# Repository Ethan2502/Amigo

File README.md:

# Amigo

A desk companion cube that takes over the things you unlock your phone for, so you have no reason to pick it up.

## Why I made it

This is my project that I got an idea for when my phone's alarm went off. I always tend to use my phone a little bit in bed when I wake up. I thought I needed my phone to wake me up but then I thought of a product that replaced all the "utility" items your phone could do but without the distractions. I used screentime apps before but they always make it in fingers reach to disable it. Amigo takes the other approach. Instead of locking the phone down, it takes over the jobs you unlock the phone for in the first place, so there is nothing to reach for.

Physically locking the phone away is something I want to add later. The current design does not do it.

## What it does

1. **Wakes you up.** Alarm clock, so your phone doesn't have to be the thing next to your bed.
2. **Keeps your phone down.** The alarm, timer, and display all live on the cube, so there is no reason to unlock your phone for any of them.
3. **Utility stuff.** Timers, stopwatch, and the other simple things you'd normally pull your phone out for.
4. **Desk toy.** Displays pictures on a slide deck while you work.
5. **Classroom toy.** Small kids in elementary school can use it to develop cognitive function with memory games or reaction time tests. It can teach them things through games where they answer questions using the keypad as arrows or other controls to move, fight, and so on. It's a lot cheaper than buying a brand new computer or phone, so it's a budget friendly classroom toy.

## How it works

Amigo is two PCBs and a 3D printed case.

The **main board** carries an ESP32-S3-WROOM-1, a TP4056 LiPo charger, an AP2112K 3.3 V LDO, and headers for the display, the audio amp, the power switch, and the button matrix. It runs off a single-cell LiPo and charges over USB-C.

The **3x3 button matrix board** is a separate PCB with nine Kailh Choc hotswap switches and nine 1N4148W diodes in a standard row/column matrix, so nine keys read over six GPIO. It connects to the main board through an 8-pin ribbon header.

## Repo layout

```
hardware/
  main-board/          KiCad project for the ESP32-S3 main board
    production/        gerbers, BOM, pick-and-place files
  button-matrix/       KiCad project for the 3x3 switch board
    libs/              Keebio-Parts footprint library (third party, see credits)
    production/
cad/
  amigo.f3z            Fusion 360 Archive file for multi-component assemblies
  step/                STEP exports
  stl/                 printable parts
docs/                  assembly instructions
firmware/              (in progress)
images/                renders and photos
bom.csv                full bill of materials
```

## Assembly

### 1. Order the PCBs

Send `hardware/main-board/production/gerbers.zip` and `hardware/button-matrix/production/gerbers.zip` to your fab house. Both are 2-layer, 1.6 mm.

You can use PCBA to save time on soldering. If you don't it will be harder and you may or may not have to make a stencil. I ordered PCBA

### 2. Print the case

| Part | File | Notes |
| --- | --- | --- |
| Case | `cad/stl/case.stl` | Needs supports |
| Button cover | `cad/stl/button-cover.stl` | 10% Gyroid |
| Display mount | `cad/stl/display-mount.stl` | 10% Gyroid |
| Keycaps | `cad/stl/keycaps.stl` | x9 10% Gyroid |

Settings I used:
1. Gyroid Infill at 10%
2. Supports only on the case
3. The rest I used bambu slicer and their default settings for PLA

### 3. Solder the main board

If you ordered PCBA then skip. 

Use solder paste, wick, and flux to do solder. I believe using a stencil will make applying solder paste easier but I ordered PCBA. Solder all the parts on to it and also
don’t forget things like key caps for the buttons. Refer to Ki Cad files as
instructions for each cap or resistor and anything else you may need. 

Also the ESP board and the TP4056 should probably be soldered first because they are the most finicky. The TP4056 also has a thermal pad underneath. I suggest soldering all the passives like capacitators and resistors last.

### 4. Solder the button matrix

When you solder the button matrix it is important to make sure your diodes are the right direction. Normally when assmbling things I find it easier to have the file open whether it be a CAD or a PCB design. This way it is concrete in exactly what direction you planned for it earlier. Also don't forget keycaps while soldering.

### 5. Wire the modules

Again you can pull up the file to see which way the order is for the pin connectors. You can then work through it wire by wire by counting. This is the most concrete way to do it withought messing up. To be extra secure you can use some hot glue and secure the connection. 

### 6. Assemble the Cube

Use M3 screws and nuts to screw everything in. There should be a hole for each screw.

### 7. Flash the Firmware

Once firmware is written you can flash it. I have not written it yet I will update it later.

## Bill of Materials

Prices are per-unit at the quantity needed to build one Amigo. Several LCSC parts have minimum order quantities well above what the board uses (the 0603 passives ship in reels of 50 or 100), so the actual amount you spend at checkout will be higher than the totals below.

The main board was ordered as PCBA, so the surface-mount parts in the first table were supplied to the assembler rather than hand-soldered. The button matrix board was ordered bare and assembled by hand.

### Main board

| Ref | Part | Qty | Unit | Total | Link |
| --- | --- | --- | --- | --- | --- |
| U3 | ESP32-S3-WROOM-1-N16R8 | 1 | $5.16 | $5.16 | [C2913202](https://www.lcsc.com/product-detail/C2913202.html) |
| U1 | TP4056-42-ESOP8 LiPo charger (ESOP-8) | 1 | $0.19 | $0.19 | [C16581](https://www.lcsc.com/product-detail/C16581.html) |
| U2 | AP2112K-3.3TRG1 LDO (SOT-23-5) | 1 | $0.11 | $0.11 | [C23380830](https://www.lcsc.com/product-detail/C23380830.html) |
| J1 | USB4085-GF-A USB-C receptacle | 1 | $1.42 | $1.42 | [C7095263](https://www.lcsc.com/product-detail/C7095263.html) |
| J2 | S2B-PH-K-S-GW JST PH 2-pin, right angle | 1 | $0.18 | $0.18 | [C157932](https://www.lcsc.com/product-detail/C157932.html) |
| J3 | PPTC081LFBN-RC female header 1x08 2.54 mm (display) | 1 | $1.54 | $1.54 | [C3320851](https://www.lcsc.com/product-detail/C3320851.html) |
| J4 | PPTC071LFBN-RC female header 1x07 2.54 mm (audio amp) | 1 | $0.79 | $0.79 | [C5342086](https://www.lcsc.com/product-detail/C5342086.html) |
| J5 | PRPC002SAAN-RC pin header 1x02 2.54 mm (power switch) | 1 | $0.09 | $0.09 | [C3346540](https://www.lcsc.com/product-detail/C3346540.html) |
| J6 | PPTC081LFBN-RC female header 1x08 2.54 mm (button ribbon) | 1 | $1.54 | $1.54 | [C3320851](https://www.lcsc.com/product-detail/C3320851.html) |
| SW1, SW2 | TL3342F260QG tactile switch | 2 | $1.15 | $2.29 | [C2886894](https://www.lcsc.com/product-detail/C2886894.html) |
| D1 | YLED0805G green LED, 0805 | 1 | $0.01 | $0.01 | [C25170728](https://www.lcsc.com/product-detail/C25170728.html) |
| D2 | YLED0805B blue LED, 0805 | 1 | $0.01 | $0.01 | [C19273154](https://www.lcsc.com/product-detail/C19273154.html) |
| D3 | YLED0805R red LED, 0805 | 1 | $0.01 | $0.01 | [C19171391](https://www.lcsc.com/product-detail/C19171391.html) |
| C1, C2, C3, C11 | 10 µF 25 V X5R, 0603 | 4 | $0.48 | $1.92 | [C344022](https://www.lcsc.com/product-detail/C344022.html) |
| C4, C6, C9, C10 | 100 nF 50 V X7R, 0603 | 4 | $0.02 | $0.08 | [C14663](https://www.lcsc.com/product-detail/C14663.html) |
| C5, C7, C8 | 1 µF 25 V X7R, 0603 | 3 | $0.02 | $0.07 | [C29936](https://www.lcsc.com/product-detail/C29936.html) |
| R1, R2 | 5.1 kΩ 1%, 0603 | 2 | $0.01 | $0.01 | [C105580](https://www.lcsc.com/product-detail/C105580.html) |
| R3 | 2 kΩ 5%, 0603 | 1 | $0.01 | $0.01 | [C105581](https://www.lcsc.com/product-detail/C105581.html) |
| R4, R5 | 100 kΩ 1%, 0603 | 2 | $0.01 | $0.01 | [C14675](https://www.lcsc.com/product-detail/C14675.html) |
| R6, R7 | 10 kΩ 1%, 0603 | 2 | $0.01 | $0.01 | [C98220](https://www.lcsc.com/product-detail/C98220.html) |
| R10, R11, R12 | 1 kΩ 1%, 0603 | 3 | $0.01 | $0.02 | [C22548](https://www.lcsc.com/product-detail/C22548.html) |
| | **Main board subtotal** | | | **$15.47** | |

### Button matrix board

| Ref | Part | Qty | Unit | Total | Link |
| --- | --- | --- | --- | --- | --- |
| CHOC1-CHOC9 | Kailh Choc low profile hotswap socket | 9 | $0.78 | $7.02 | [Amazon](https://www.amazon.com/Mechkeeb-Kailh-Low-Hot-swappable-Socket/dp/B0BS3L174L) |
| | Kailh Choc low profile keyswitch | 9 | $1.92 | $17.28 | [Amazon](https://www.amazon.com/KAILH-Official-Chocolate-Mechanical-Keyboard/dp/B0B3MNBPSP) |
| D1-D9 | 1N4148W diode, SOD-123 | 9 | $0.01 | $0.08 | [C908248](https://www.lcsc.com/product-detail/C908248.html) |
| J1 | Header 1x08 2.54 mm (ribbon to main board) | 1 | $1.54 | $1.54 | [C3320851](https://www.lcsc.com/product-detail/C3320851.html) |
| R1, R2, R3 | 10 kΩ 1%, 0603 | 3 | $0.01 | $0.02 | [C98220](https://www.lcsc.com/product-detail/C98220.html) |
| | **Button matrix subtotal** | | | **$25.94** | |

Keycaps are 3D printed from `cad/stl/keycaps.stl`, so there is nothing to buy for them.

### Off-board parts

| Part | Qty | Unit | Total | Link |
| --- | --- | --- | --- | --- |
| HiLetgo 2.8 in ILI9341 SPI display, 240x320 | 1 | $16.39 | $16.39 | [Amazon](https://www.amazon.com/HiLetgo-240X320-Resolution-Display-ILI9341/dp/B073R7BH1B) |
| MAX98357A I2S audio amp breakout | 1 | $6.88 | $6.88 | [Amazon](https://www.amazon.com/MAX98357-MAX98357A-Amplifier-Interface-Raspberry/dp/B0DPJRLMDJ) |
| CQRobot speaker, JST-PH 2.0 mm interface | 1 | $7.99 | $7.99 | [Amazon](https://www.amazon.com/CQRobot-JST-PH2-0-Interface-Electronic-Projects/dp/B0738NLFTG) |
| EEMB 1100 mAh single-cell LiPo, JST connector | 1 | $6.15 | $6.15 | [Amazon](https://www.amazon.com/EEMB-1100mAh-Battery-Rechargeable-Connector/dp/B08VRYS8FT) |
| Rocker power switch | 1 | $1.35 | $1.35 | [AliExpress](https://www.aliexpress.us/item/3256812208202705.html) |
| Jumper wires, board-to-board ribbon link | 1 | $6.98 | $6.98 | [Amazon](https://www.amazon.com/Elegoo-EL-CP-004-Multicolored-Breadboard-arduino/dp/B01EV70C78) |
| PLA filament for case, button cover, display mount, keycaps | 1 | $20.00 | $20.00 | [Polymaker](https://shop.polymaker.com/products/polymaker-pla-pro?variant=41550910652473) |
| M3 screws and nuts pack of 100 | 1 | $15.30 | $15.30 | [McMaster](https://www.mcmaster.com/products/screws/socket-head-screws-2~/steel-socket-head-screws~~/?s=m3+screws) |
| PCB fabrication: main board PCBA and button matrix bare PCB | 1 | $50.65 | $50.65 | [JLCPCB](https://jlcpcb.com/) |
| | | | **$131.69 plus fasteners** | |

The Amazon parts ship in fixed pack sizes rather than the exact count the build uses. The Unit column is the per-item price and the Total is what one Amigo consumes, so your checkout total will be higher.

### Total

**$173.10 plus fasteners** to build one Amigo: $15.47 for the main board, $25.94 for the button matrix, and $116.39 in off-board parts and fabrication. Fabrication is the single largest line at $50.65.

## Tools used

Not part of the build, listed for anyone reproducing it.

| Tool | Link |
| --- | --- |
| Soldering iron | [Amazon](https://www.amazon.com/Wonderway-Soldering-Electronics-CELLPHONE-Repairing/dp/B0BLSJQPR6) |
| Desoldering pump | [Amazon](https://www.amazon.com/Lesnow-Desoldering-Electronics-Disassemble-Electrical/dp/B0F8BJPC9Y) |
| Multimeter | [Amazon](https://www.amazon.com/ANENG-Multimeter-Resistance-Continuity-Automotive/dp/B0BYD32JZV) |

## Firmware

Not written yet. The plan is firmware that lets people program the device, download or make games, and customize it for their needs, with over-the-wifi updates so the software keeps getting better.

## Credits

The `hardware/button-matrix/libs/Keebio-Parts.pretty-master` footprint library is Keebio's, used under its own license for the Kailh Choc footprints. Everything else in this repo is my own work.

## What I learned

I used a bunch of stuff on this project for the first time, like KiCad to make my PCBs. I realize how hard it is to actually verify if some PCB works before you order it. I guess it is because I didn't have a breadboard kit. Some of the most memorable things I learned about electronic design is things like not forgetting a fuse or remembering to add EN and Boot switches. I also learned to try and plan the actual product out before because I wanted motors to drive it but I didn't account for any sizing constraints and it turned out to be to out of reach for a first project.

I really enjoyed putting everything together at the end in Fusion with the actual CAD of the PCB. My least faveorite part was actually ordering everything because who knew things cost money! I didn't notice but my amazon cart added up quick and I made a switch to ali express and was able to save some money. JLC was also really annoying one day where it kept rejecting my files and it didn't work and I had to restart the entire process from scratch to try and debug it. Another thing I learned while ordering was the company LCSC sells parts but it takes time to quote it. They sent me an email but I didn't check it so I forgot to actually order it! Overall I am excited to assmble this thing I have been working on for a long time.

---

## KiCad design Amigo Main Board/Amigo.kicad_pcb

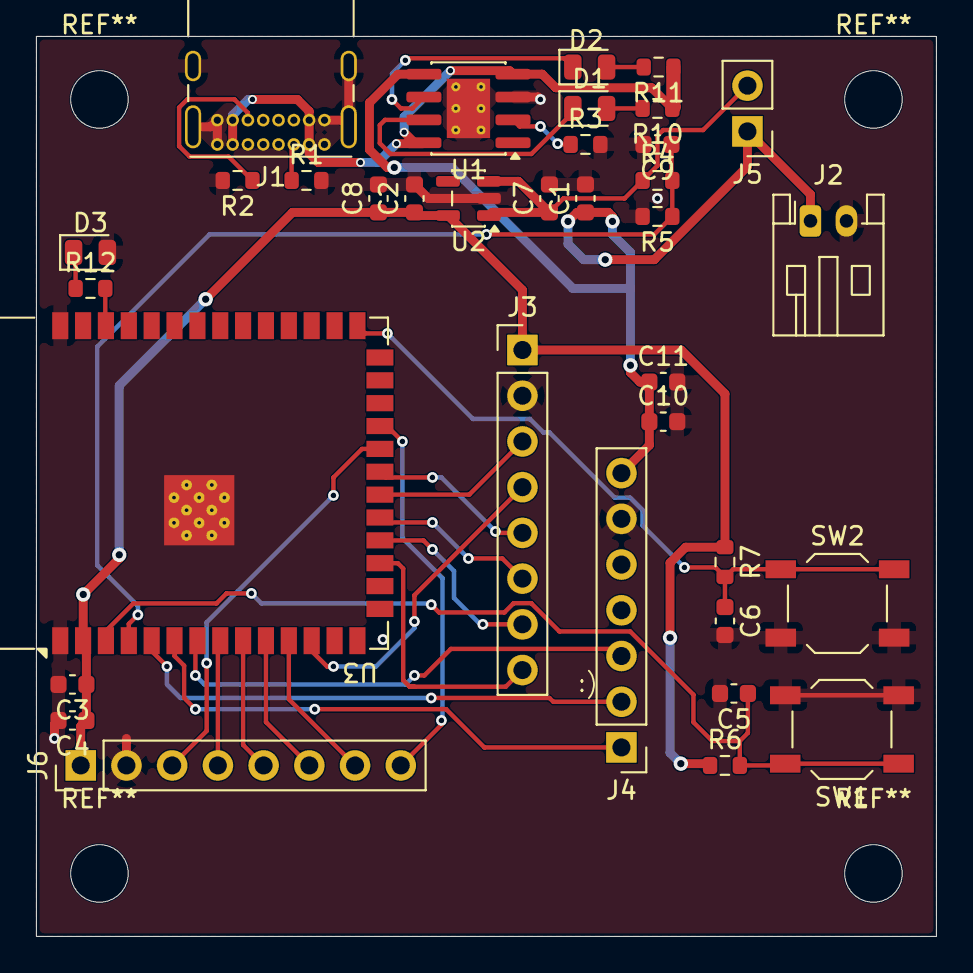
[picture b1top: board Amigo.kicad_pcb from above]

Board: 2 copper layers, 50.0 x 50.0 mm, 35 parts (0 on the bottom side), 32 nets.

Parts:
C1, C2, C3, C11: 10µF; C_0603_1608Metric
C4, C6, C9, C10: 100nF; C_0603_1608Metric
C5, C7, C8: 1µF; C_0603_1608Metric
D1, D2, D3: LED; LED_0805_2012Metric
J1: USB_C_Receptacle_USB2.0_16P; USB_C_Receptacle_GCT_USB4085
J2: Conn_01x02; JST_PH_S2B-PH-K_1x02_P2.00mm_Horizontal
J3: OLED; PinHeader_1x08_P2.54mm_Vertical
J4: MAX98357A; PinHeader_1x07_P2.54mm_Vertical
J5: Rocker Switch; PinHeader_1x02_P2.54mm_Vertical
J6: ButtonRibbonConnector; PinHeader_1x08_P2.54mm_Vertical
R1, R2: 5.1k; R_0603_1608Metric
R3: 2k; R_0603_1608Metric
R4, R5: 100k; R_0603_1608Metric
R6, R7: 10k; R_0603_1608Metric
R10, R11, R12: 1k; R_0603_1608Metric
SW1, SW2: SW_Push; SW_SPST_TL3342
U1: TP4056-42-ESOP8; SOIC-8-1EP_3.9x4.9mm_P1.27mm_EP2.41x3.3mm_ThermalVias
U2: AP2112K-3.3; SOT-23-5
U3: ESP32-S3-WROOM-1

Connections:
+3V3: C2.1, C3.1, C4.1, C8.1, J3.1, J6.1, R6.1, R7.1, U2.5 (VOUT), U3.2 (3V3)
AUDIO_BCLK: J4.2, U3.5 (IO5)
AUDIO_DOUT: J4.3, U3.7 (IO7)
AUDIO_LRC_WS: J4.1, U3.6 (IO6)
BAT+: C1.1, C10.1, C11.1, J2.1, J4.7, J5.1, U1.5 (BAT)
BAT_SENSE: C9.1, R4.2, R5.1, U3.4 (IO4)
BAT_SW: C7.1, J5.2, R4.1, U2.1 (VIN), U2.3 (EN)
BUTTON_COL_0: J6.6, U3.10 (IO17)
BUTTON_COL_1: J6.7, U3.11 (IO18)
BUTTON_COL_2: J6.8, U3.23 (IO21)
BUTTON_ROW_0: J6.3, U3.22 (IO14)
BUTTON_ROW_1: J6.4, U3.8 (IO15)
BUTTON_ROW_2: J6.5, U3.9 (IO16)
EN: C5.1, R6.2, SW1.1, U3.3 (EN)
GND: C1.2, C2.2, C3.2, C4.2, C5.2, C6.2, C7.2, C8.2, C9.2, C10.2, C11.2, D3.2 (A), J1.A1 (GND), J1.A12 (GND), J1.B1 (GND), J1.B12 (GND), J1.SH (SHIELD), J2.2, J3.2, J4.6, J6.2, R1.2, R2.2, R3.2, R5.2, SW1.2, SW2.2, U1.3 (GND), U1.9 (EPAD), U2.2 (GND), U3.1 (GND), U3.40 (GND), U3.41 (GND)
IO0: C6.1, R7.2, SW2.1, U3.27 (IO0)
LCD_BL: J3.8, U3.17 (IO9)
LCD_CS: J3.3, U3.20 (IO12)
LCD_DC: J3.5, U3.21 (IO13)
LCD_MOSI: J3.6, U3.19 (IO11)
LCD_RST: J3.4, U3.12 (IO8)
LCD_SCK: J3.7, U3.18 (IO10)
LED_STATUS: R12.2, U3.38 (IO2)
unnamed: D1.2 (A), R10.2
unnamed: D1.1 (K), U1.7 (~CHRG)
unnamed: D2.2 (A), R11.2
unnamed: D2.1 (K), U1.6 (~STDBY)
unnamed: D3.1 (K), R12.1
unnamed: R3.1, U1.2 (PROG)
USB_CC1: J1.A5 (CC1), R1.1
USB_CC2: J1.B5 (CC2), R2.1
VBUS_5V: J1.A4 (VBUS), J1.A9 (VBUS), J1.B4 (VBUS), J1.B9 (VBUS), R10.1, R11.1, U1.4 (V_{CC}), U1.8 (CE)

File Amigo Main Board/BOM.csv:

"Id";"Designator";"Footprint";"Quantity";"Designation";"Supplier and ref";
1;"C1, C2, C3, C11";"C_0603_1608Metric";4;"10µF";;;
2;"C4, C6, C9, C10";"C_0603_1608Metric";4;"100nF";;;
3;"C5, C7, C8";"C_0603_1608Metric";3;"1µF";;;
4;"D1, D2, D3";"LED_0805_2012Metric";3;"LED";;;
5;"J1";"USB_C_Receptacle_GCT_USB4085";1;"USB_C_Receptacle_USB2.0_16P";;;
6;"J2";"JST_PH_S2B-PH-K_1x02_P2.00mm_Horizontal";1;"Conn_01x02";;;
7;"J3";"PinHeader_1x08_P2.54mm_Vertical";1;"OLED";;;
8;"J4";"PinHeader_1x07_P2.54mm_Vertical";1;"MAX98357A";;;
9;"J5";"PinHeader_1x02_P2.54mm_Vertical";1;"Rocker Switch";;;
10;"J6";"PinHeader_1x08_P2.54mm_Vertical";1;"ButtonRibbonConnector";;;
11;"R1, R2";"R_0603_1608Metric";2;"5.1k";;;
12;"R3";"R_0603_1608Metric";1;"2k";;;
13;"R4, R5";"R_0603_1608Metric";2;"100k";;;
14;"R6, R7";"R_0603_1608Metric";2;"10k";;;
15;"R10, R11, R12";"R_0603_1608Metric";3;"1k";;;
16;"SW1, SW2";"SW_SPST_TL3342";2;"SW_Push";;;
17;"U1";"SOIC-8-1EP_3.9x4.9mm_P1.27mm_EP2.41x3.3mm_ThermalVias";1;"TP4056-42-ESOP8";;;
18;"U2";"SOT-23-5";1;"AP2112K-3.3";;;
19;"U3";"ESP32-S3-WROOM-1";1;"ESP32-S3-WROOM-1";;;

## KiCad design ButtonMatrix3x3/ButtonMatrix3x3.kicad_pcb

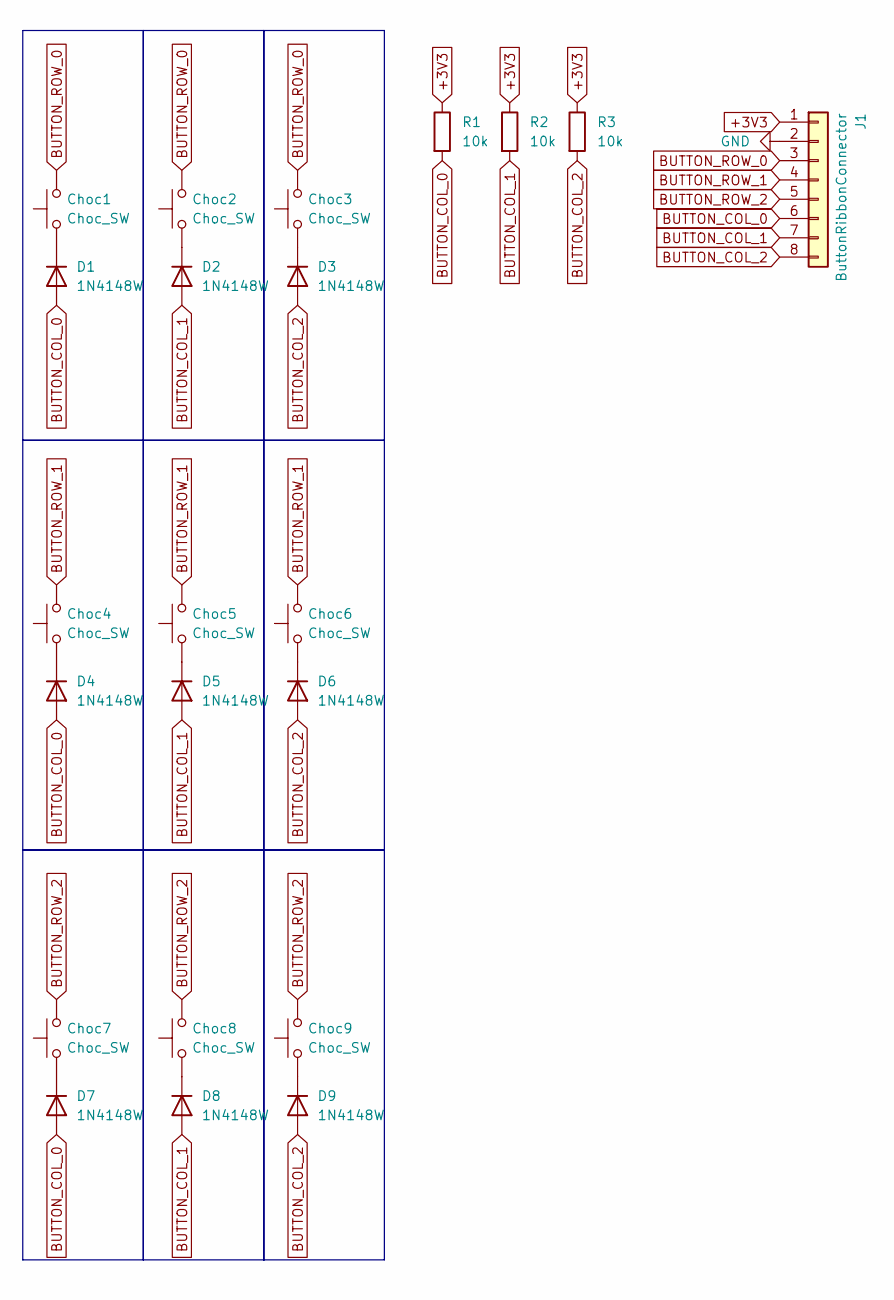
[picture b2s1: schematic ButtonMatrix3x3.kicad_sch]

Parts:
Choc1, Choc2, Choc3, Choc4, Choc5, Choc6, Choc7, Choc8, Choc9: Choc_SW; SW_choc_v1+v2_HS_CPG135001S30_1u
D1, D2, D3, D4, D5, D6, D7, D8, D9: 1N4148W; D_SOD-123
J1: ButtonRibbonConnector; PinHeader_1x08_P2.54mm_Vertical
R1, R2, R3: 10k; R_0603_1608Metric

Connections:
+3V3: J1.1, R1.1, R2.1, R3.1
BUTTON_COL_0: D1.2 (A), D4.2 (A), D7.2 (A), J1.6, R1.2
BUTTON_COL_1: D2.2 (A), D5.2 (A), D8.2 (A), J1.7, R2.2
BUTTON_COL_2: D3.2 (A), D6.2 (A), D9.2 (A), J1.8, R3.2
BUTTON_ROW_0: Choc1.2, Choc2.2, Choc3.2, J1.3
BUTTON_ROW_1: Choc4.2, Choc5.2, Choc6.2, J1.4
BUTTON_ROW_2: Choc7.2, Choc8.2, Choc9.2, J1.5
GND: J1.2
unnamed: Choc1.1, D1.1 (K)
unnamed: Choc2.1, D2.1 (K)
unnamed: Choc3.1, D3.1 (K)
unnamed: Choc4.1, D4.1 (K)
unnamed: Choc5.1, D5.1 (K)
unnamed: Choc6.1, D6.1 (K)
unnamed: Choc7.1, D7.1 (K)
unnamed: Choc8.1, D8.1 (K)
unnamed: Choc9.1, D9.1 (K)

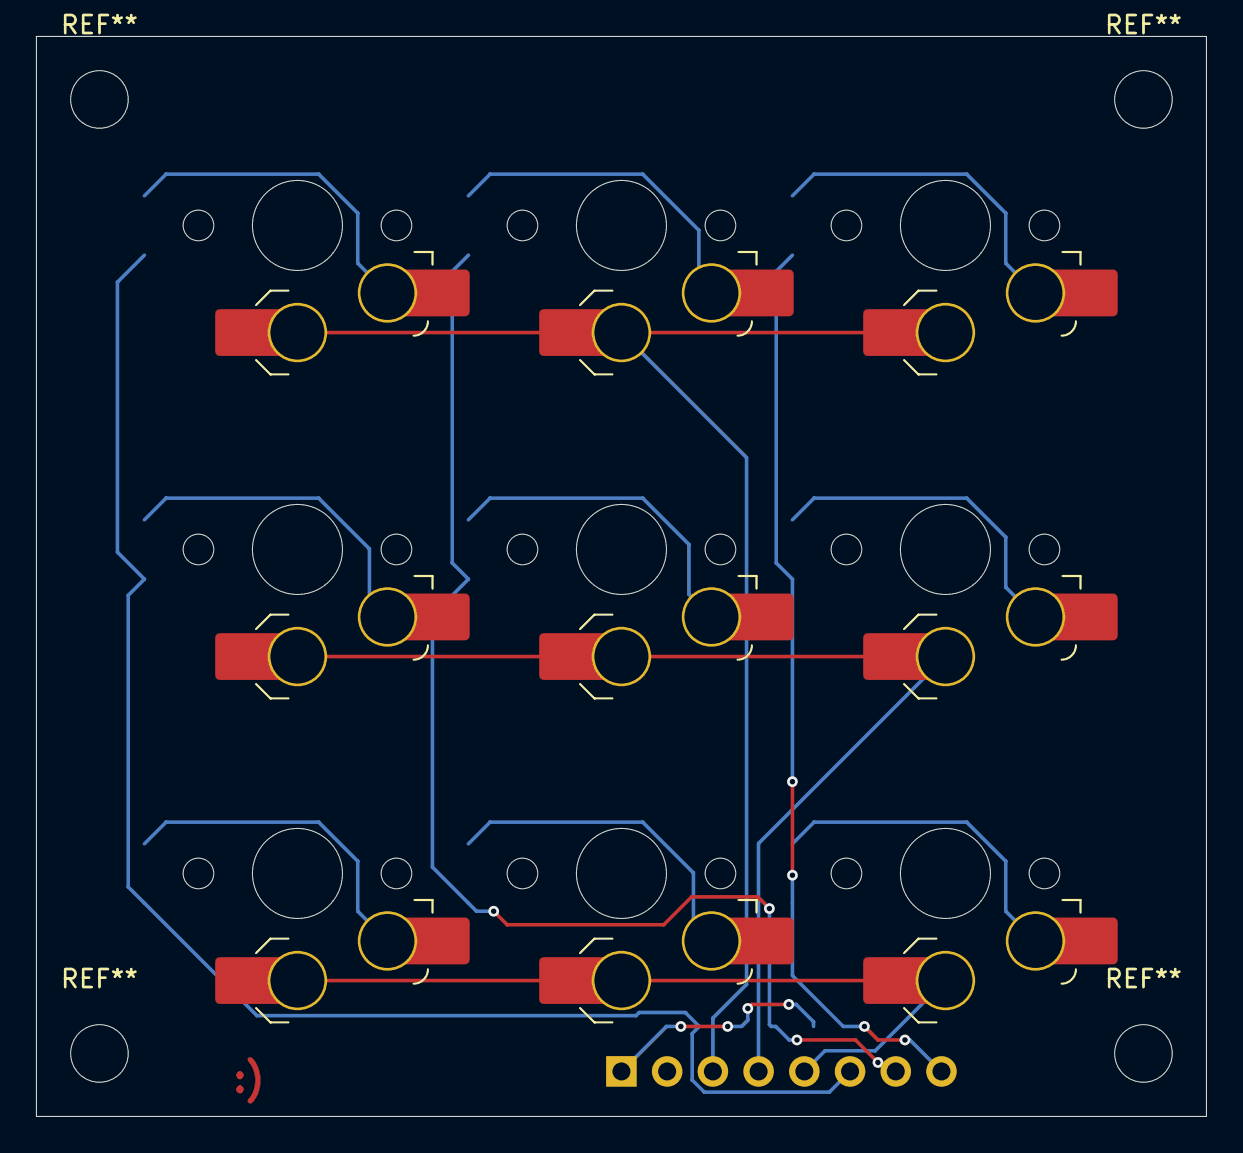
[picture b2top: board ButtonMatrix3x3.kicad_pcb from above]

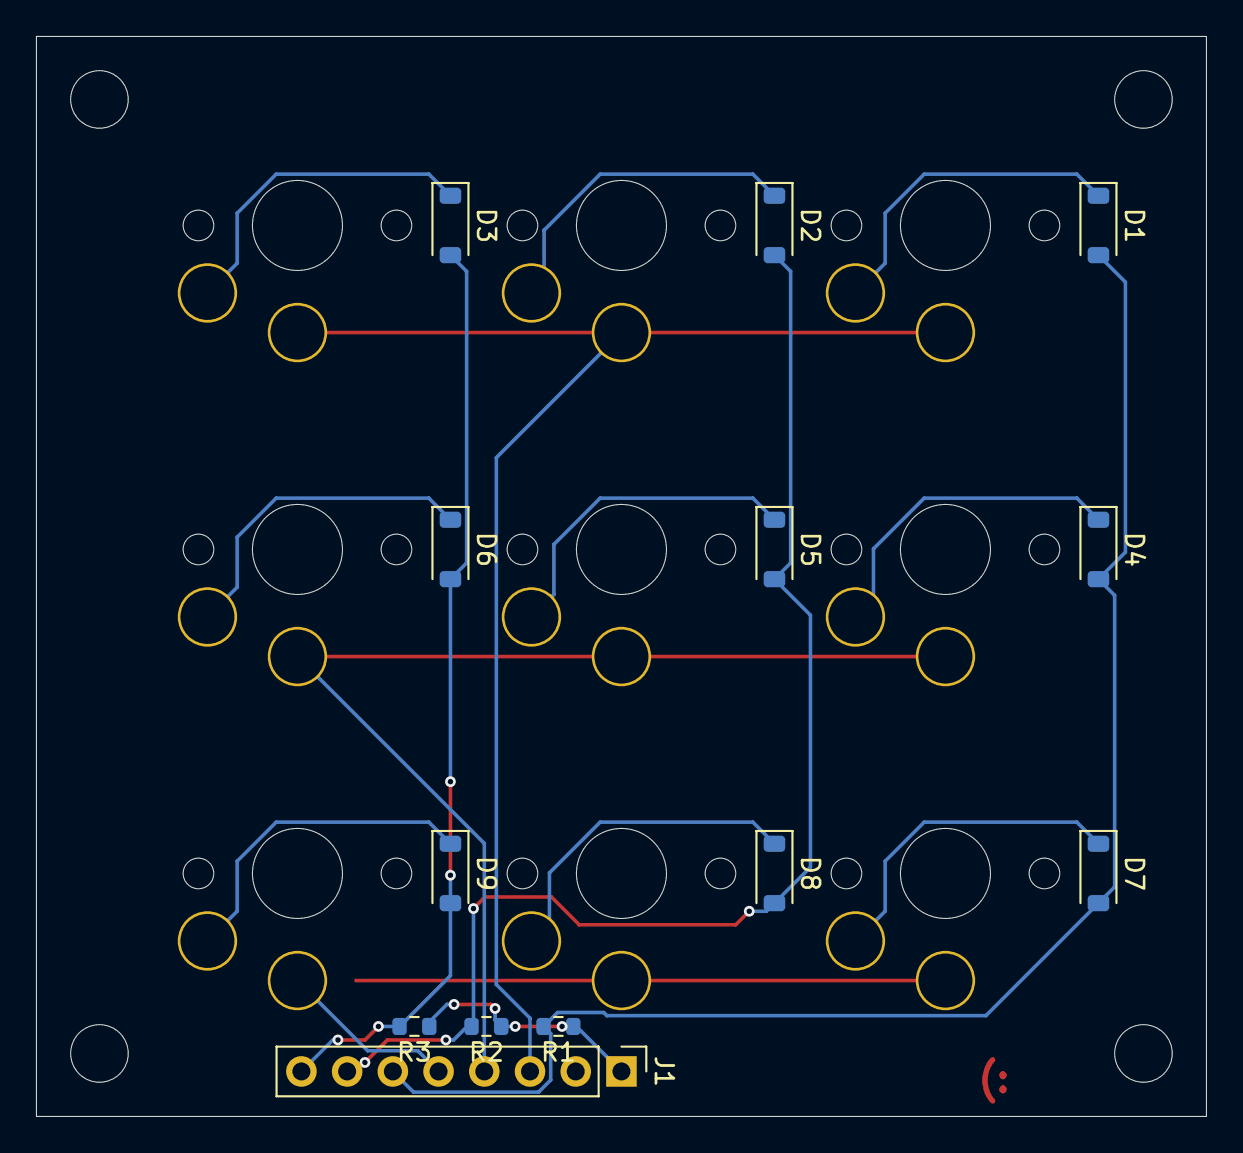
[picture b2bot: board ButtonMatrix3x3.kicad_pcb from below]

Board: 2 copper layers, 65.0 x 60.0 mm, 22 parts (13 on the bottom side), 16 nets.

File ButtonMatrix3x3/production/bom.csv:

Designator,Footprint,Quantity,Value,LCSC Part #
"CHOC1, CHOC2, CHOC3, CHOC4, CHOC5, CHOC6, CHOC7, CHOC8, CHOC9",SW_choc_v1+v2_HS_CPG135001S30_1u,9,Choc_SW,
"D1, D2, D3, D4, D5, D6, D7, D8, D9",D_SOD-123,9,1N4148W,
J1,PinHeader_1x08_P2.54mm_Vertical,1,ButtonRibbonConnector,
"R1, R2, R3",0603,3,10k,

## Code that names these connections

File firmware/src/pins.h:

// pins.h -- Amigo GPIO map, transcribed from the ESP32-S3-WROOM-1 schematic sheet.
#pragma once

// Status LED
constexpr int PIN_LED_STATUS = 2;

// Battery sense (ADC1_CH3, safe to use with WiFi active)
constexpr int PIN_BAT_SENSE = 4;

// MAX98357A I2S audio
constexpr int PIN_AUDIO_BCLK = 5;
constexpr int PIN_AUDIO_LRC = 6;
constexpr int PIN_AUDIO_DOUT = 7;

// MAX98357A SD_MODE. Not routed on rev A: this is the bodge wire from J4 pin 5
// to the IO38 castellated pad. Comment out AUDIO_SD_CONNECTED to build for a
// board without the wire, in which case the amp is always on.
#define AUDIO_SD_CONNECTED 1
constexpr int PIN_AUDIO_SD = 38;

// ILI9341 2.8" SPI display
constexpr int PIN_LCD_RST = 8;
constexpr int PIN_LCD_BL = 9;
constexpr int PIN_LCD_SCK = 10;
constexpr int PIN_LCD_MOSI = 11;
constexpr int PIN_LCD_CS = 12;
constexpr int PIN_LCD_DC = 13;

// Kailh Choc 3x3 matrix
constexpr int PIN_ROW[3] = {14, 15, 16};
constexpr int PIN_COL[3] = {17, 18, 21};

// Backlight PWM (LEDC)
constexpr int BL_LEDC_CHANNEL = 0;
constexpr int BL_LEDC_FREQ_HZ = 5000;
constexpr int BL_LEDC_RES_BITS = 8;

// Battery divider: R4 100k (BAT_SW to tap) / R5 100k (tap to GND), tap on IO4,
// filtered by C9 100nF. Ratio = (R4 + R5) / R5 = 2.0. Confirmed from schematic.
constexpr float BAT_DIVIDER_RATIO = 2.0f;

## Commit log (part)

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2026-05-05 initial commit with some parts added in
2026-05-06 Power section complete
    Schematic Power section
2026-05-06 added .history to .gitignore
2026-05-06 updated gitignor
2026-05-06 Fix: Stop tracking ignored files
2026-05-06 Wired up ESP board with all the stuff
2026-05-07 Finished wiring audio amp in schematic
2026-05-07 Finished wiring motor controller in schematic
2026-05-07 Finished button matrix in schematic. Ready to move on to PCB
2026-05-08 PCB updating and annotating
2026-05-10 Clean start in Amigo folder
2026-05-11 Main PCB placement
2026-05-17 PCB wiring done
2026-05-19 Wiring first draft done. Will start the rewiring and try to avoid DRC errors
2026-05-19 Positioned Everything
2026-05-21 Fixed all DRC errors, Added groundpour
2026-05-21 fixed LED polarity
2026-05-21 Gerbers generated
2026-05-21 pcb? I don't think it is updated on git
2026-05-21 Found out why there is a discrepancy with two main board files. The real one is in the Main Board folder
2026-05-23 Before removal of motors and OLED change
2026-05-24 Finished wiring up the new OLED
2026-05-25 Debugged an unconnected error and generated step and gerber
2026-05-25 Fix another DRC error and rotated battery JST connector
2026-05-31 idk tbh
2026-06-22 gerber and stuff
2026-06-28 Steps and Stls
2026-06-29 README and Assembly Instructions
